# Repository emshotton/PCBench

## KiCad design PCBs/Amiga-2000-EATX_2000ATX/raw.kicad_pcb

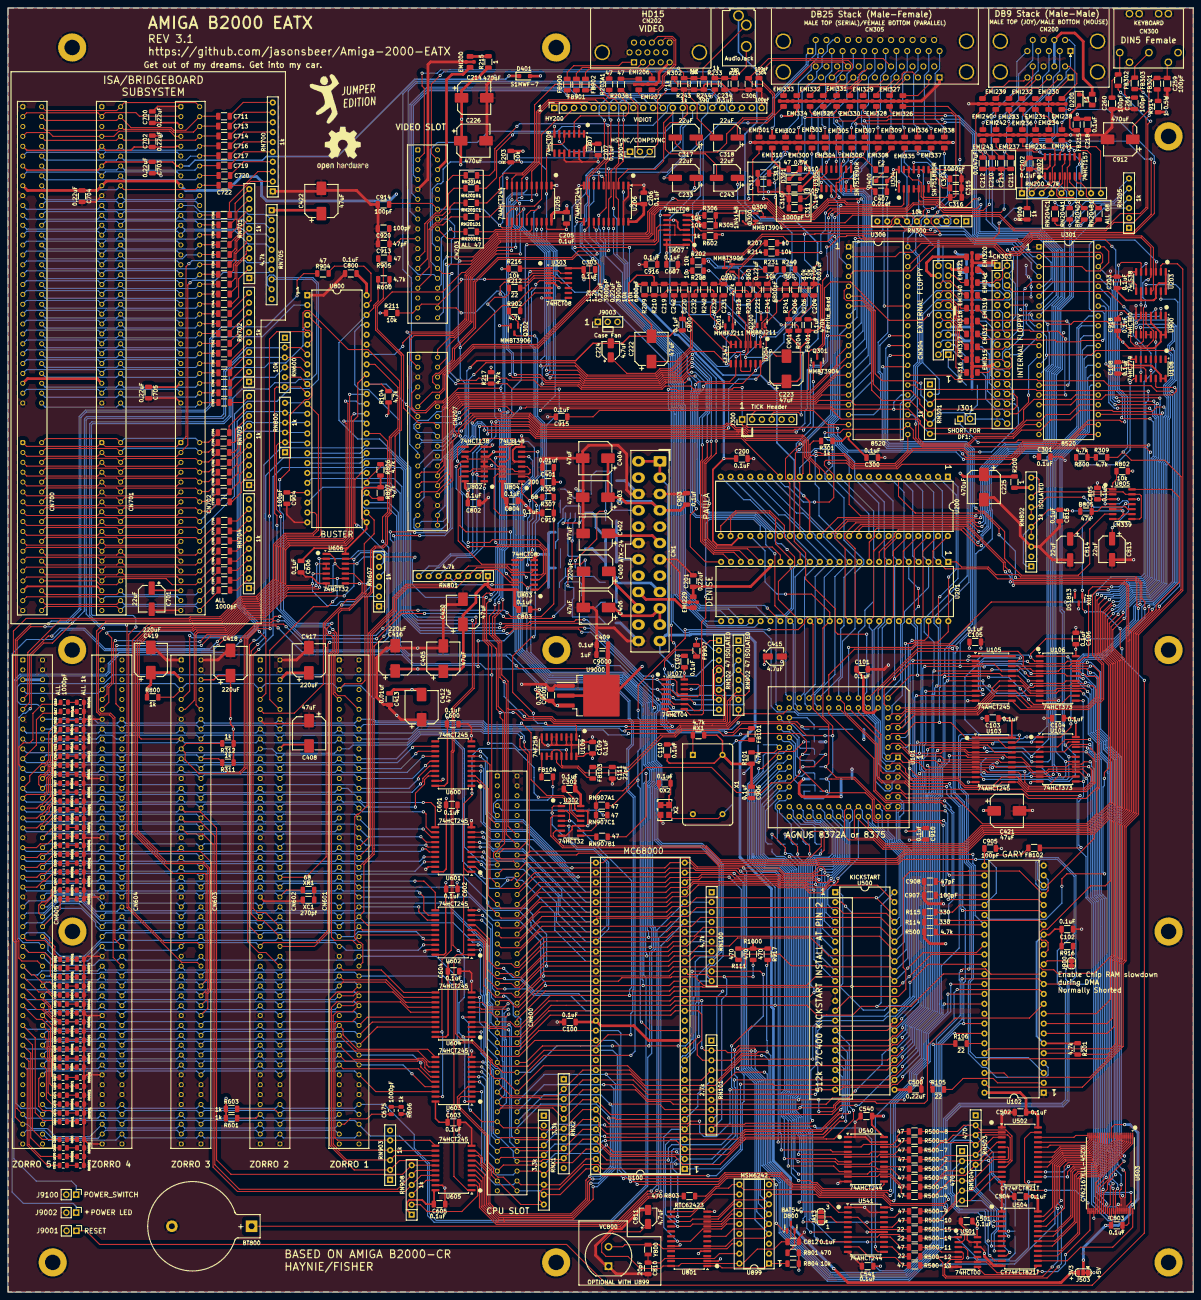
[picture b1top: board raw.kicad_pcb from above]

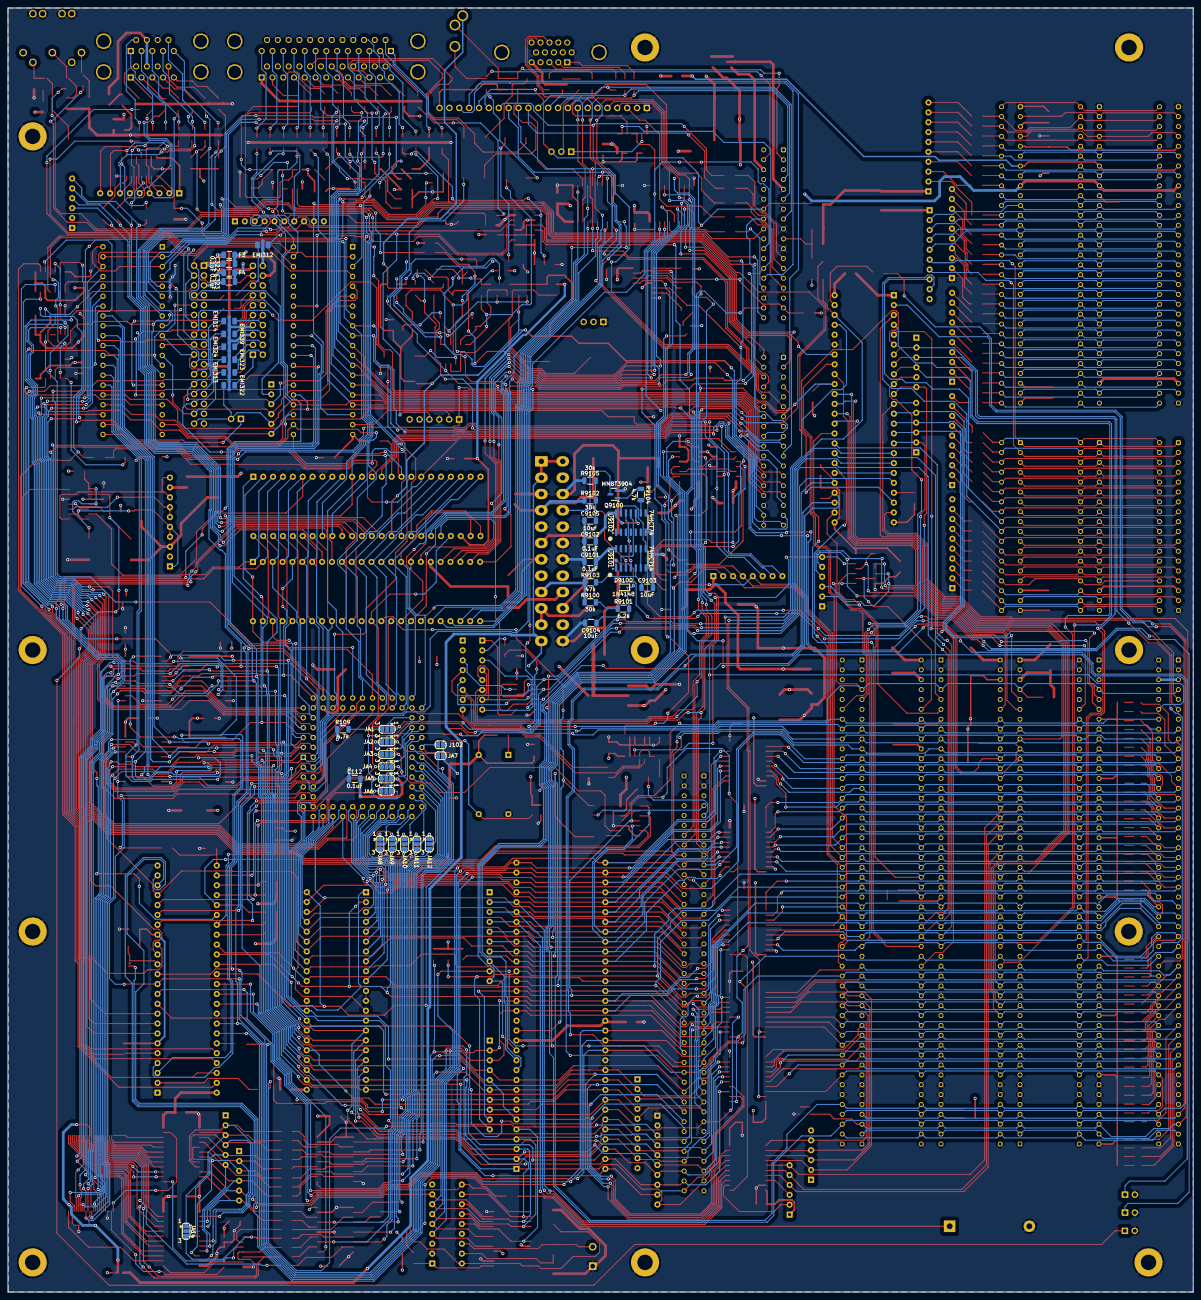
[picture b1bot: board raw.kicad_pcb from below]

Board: 4 copper layers, 304.8 x 330.2 mm, 612 parts (42 on the bottom side), 793 nets.

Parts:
BT800: Battery_Cell; BatteryHolder_Keystone_103_1x20mm
C100, C101, C102, C103, C104, C105, C106, C107, C108, C109, C110, C112, C200, C202, C203, C205, C206, C207, C218, C234, C244, C300, C301, C302, C303, C305, C322, C323, C501, C502, C503, C504, C540, C541, C600, C601, C602, C603, C604, C605, C606, C607, C800, C802, C803, C804, C805, C812, C815, C900, C901, C915, C916, C918, C919, C9101, C9102: 0.1uF; C_1206_3216Metric
C111: 22pF; C_1206_3216Metric
C201, C219, C220, C221, C500, C700, C702, C703, C704, C705: 0.22uF; C_1206_3216Metric
C204: 0.01uF; C_1206_3216Metric
C210, C211, C212, C213: 0.047uF; C_1206_3216Metric
C214, C225, C226, C912: 470uF; CP_Elec_8x10
C222, C223, C402, C403, C404, C405, C406, C408, C412, C420, C421, C422: 47uF; CP_Elec_8x10
C224, C415, C811: 4.7uF; CP_Elec_4x5.8
C231, C241: 6800pF; C_1206_3216Metric
C232, C242: 3900pF; C_1206_3216Metric
C233, C243, C317, C318, C701, C813, C814: 22uF; CP_Elec_6.3x5.8
C259, C260, C261, C304, C306, C904, C905, C907, C914, C920: 100pF; C_1206_3216Metric
C310, C311, C312, C313, C314, C315, C316, C711, C713, C714, C716, C717, C719, C720, C722, C726, C728, C730, C732, C734, C736, C738, C740, C742, C744, C746, C748, C750, C752, C754, C756, C758, C760, C762, C764, C766, C768, C770, C776, C778, C780, C782, C784, C786, C787, C789, C790, C791, C793, C794, C796: 1000pF; C_1206_3216Metric
C400, C416, C417, C418, C419: 220uF; CP_Elec_8x10
C401, C407, C413: 0.01uf; C_1206_3216Metric
C409, C903, C906, C910: 0.1uf; C_1206_3216Metric
C617, C619, C620, C621, C622, C623, C624, C625, C626, C627, C628, C629, C630, C631, C632, C633, C635, C637, C639, C641, C645, C647, C649, C650, C651, C652, C654, C655, C657, C658, C659, C660, C661, C662, C663, C664, C665, C666, C667, C668, C669, C670, C671, C672, C673, C674, C675: 1000pF; C_0805_2012Metric
C810: 20pF; C_1206_3216Metric
C908, C913: 47pF; C_1206_3216Metric
C9000: 1uF; C_1206_3216Metric
C9001: 0.33uF; C_1206_3216Metric
C9103, C9104, C9105: 10uF; C_1206_3216Metric
CN1: ATX-24; Molex_Mini-Fit_Jr_5566-24A_2x12_P4.20mm_Vertical
CN200: DB9_Male_Stack; DSUB-9_Male_Stack
CN202: DB15_Female_HighDensity; DSUB-15-HD_Female_Horizontal_P2.29x1.98mm_EdgePinOffset8.35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
CN203, CN207: Amiga-2000-Video-Slot; 2x18_P2.54mm_Horizontal
CN205: AudioJack; Jack_3.5mm_CUI_SJ1-3533NG_Horizontal_CircularHoles
CN300: KEYBOARD; DIN5
CN303: INTERNAL FLOPPY; PinHeader_2x17_P2.54mm_Vertical
CN304: EXTERNAL FLOPPY; PinHeader_2x10_P2.54mm_Vertical
CN305: DB25_Stack_FemaleAndMale; DSUB-25_Stack_Female_Bottom_Male_Top
CN600: Amiga-2000-CPU-Slot; Samtec_HLE-150-02-xx-DV-TE_2x43_P2.54mm_Horizontal
CN601, CN602, CN603, CN604, CN605: Amiga-2000-Zorro-Slot; Samtec_HLE-150-02-xx-DV-TE_2x50_P2.54mm_Horizontal
CN700, CN701, CN702: ISA-16-BIT-Slot; ISA_16-BIT_P2.54mm_Horizontal
CX2: 0.1uF; C_1206_3216Metric
D200, D301, D400, D401: S1MWF-7; D_SOD-123F
D300, D9100: 1N4148; D_SOD-323
D800: BAT54C; SOT-23
EMI200, EMI206, EMI207, EMI229, EMI230, EMI231, EMI232, EMI233, EMI234, EMI235, EMI236, EMI237, EMI238, EMI239, EMI240, EMI241, EMI242, EMI243, EMI300, EMI301, EMI302, EMI303, EMI304, EMI305, EMI306, EMI307, EMI308, EMI309, EMI310, EMI311, EMI312, EMI313, EMI314, EMI315, EMI316, EMI317, EMI318, EMI319, EMI320, EMI321, EMI322, EMI323, EMI324, EMI325, EMI326, EMI327, EMI328, EMI329, EMI330, EMI331, EMI332, EMI333, EMI334, EMI335, EMI336, EMI337, EMI338, EMI339, EMI340, EMI341: 100pF; C_1206_3216_Feedthrough
F1, F2: 4A; Fuse_1206_3216Metric
F3, F4: Fuse; Fuse_1206_3216Metric
FB101, FB102, FB103, FB104, FB215, FB301, FB302, FB303, FB401, FB900, FB901, FB902, FB907: Ferrite_Bead; C_1206_3216Metric
H1, H2, H3, H4, H5, H6, H7, H9, H10, H11, H12: MountingHole_Pad
HY200: VIDIOT; PinSocket_1x22_P2.54mm_Vertical
J102: Short for 8327A NTSC or 8375; SolderJumper-2_P1.3mm_Open_RoundedPad1.0x1.5mm
J300: TICK Header; PinHeader_1x06_P2.54mm_Vertical
J301: SHORT FOR DF1; PinHeader_1x02_P2.54mm_Vertical
J503: Mcc; SolderJumper-3_P1.3mm_Bridged12_RoundedPad1.0x1.5mm
J900: Enable Chip RAM slowdown during DMA; SolderJumper-2_P1.3mm_Bridged_RoundedPad1.0x1.5mm
J9001: RESET; PinHeader_1x02_P2.54mm_Vertical
J9002: POWER LED; PinHeader_1x02_P2.54mm_Vertical
J9003: Case Fan; FanHeader_1x03_P2.54mm_Vertical
J9004: HSYNC/COMPSYNC; PinHeader_1x03_P2.54mm_Vertical
J9100: POWER_SWITCH; PinHeader_1x02_P2.54mm_Vertical
JA1, JA2, JA3, JA4, JA5, JA6, JA8, JA9, JA10, JA11, JA12, JA13, JA14: 8375/8372A; SolderJumper-3_P1.3mm_Open_RoundedPad1.0x1.5mm
JA7: 8372A; SolderJumper-2_P1.3mm_Open_RoundedPad1.0x1.5mm
Q200, Q201: MMBFJ211; SOT-23
Q202, Q302: MMBT3906; SOT-23
Q300, Q301, Q9100: MMBT3904; SOT-23
R101, R104, R109, R201, R217, R300, R309, R500, R600, R806, R807, R902, R916, R9104: 4.7k; R_1206_3216Metric
R105, R106, R212, R500-12, R500-14, R500-15: 22; R_1206_3216Metric
R111, R801, R803, R917, R1000: 470; R_1206_3216Metric
R114, R115: 330; R_1206_3216Metric
R200, R215: 1; R_1206_3216Metric
R202, R203, R206, R211, R214, R216, R231, R232, R241, R242, R305, R306, R802, R804: 10k; R_1206_3216Metric
R203A1, R203B1, R500-1, R500-2, R500-3, R500-4, R500-5, R500-6, R500-7, R500-8, R500-9, R500-10, R500-11, R500-13, R904, R905: 47; R_1206_3216Metric
R204, R205: 470k; R_1206_3216Metric
R207, R208: 10; R_1206_3216Metric
R209, R210: 1.2k; R_1206_3216Metric
R213: 2.7k; R_1206_3216Metric
R230, R240: 360; R_1206_3216Metric
R233, R243, R301, R302, R311, R312, R601, R602, R603, R800, R900: 1k; R_1206_3216Metric
R234, R244: 390; R_1206_3216Metric
R307: 68; R_1206_3216Metric
R308: 200; R_1206_3216Metric
R310: 47 0.5W; R_1206_3216Metric
R601A1, R601B1, R601C1, R601D1, R601E1, R601F1, R601G1, R601H1, R601I1, R602A1, R602B1, R602C1, R602D1, R602E1, R602F1, R602G1, R602H1, R602I1, R603A1, R603B1, R603C1, R603D1, R603E1, R603F1, R603G1, R603H1, R603I1, R604, R604A1, R604B1, R604C1, R604D1, R604E1, R604F1, R604G1, R604H1, R604I1, R605, R605A1, R605B1, R605C1, R605D1, R605E1, R605F1, R605G1, R605H1, R606: 1k; R_0805_2012Metric
R805, R9103: 47k; R_1206_3216Metric
R914: 1 0.5W; R_1206_3216Metric
R9100, R9102, R9105: 30k; R_1206_3216Metric
R9101: 6.2k; R_1206_3216Metric
RN100, RN705: 4.7k; R_Array_SIP10
RN101: 2.7k; R_Array_SIP10
RN102, RN902: 47; R_Array_SIP8
RN200: 4.7k; R_Array_SIP9
RN201A1, RN201B1, RN201C1, RN201D1, RN203E1, RN907A1, RN907B1, RN907C1: 47; R_1206_3216Metric
RN204A1, RN204B1, RN204C1, RN204D1: 68; R_1206_3216Metric
RN205, RN301, RN607, RN800, RN903, RN908: 1k; R_Array_SIP6
RN300: 10k; R_Array_SIP10
RN503, RN504: 470; R_Array_SIP6
RN600: 10k; R_Array_SIP6
RN700, RN701, RN702, RN703, RN704, RN802: 1k; R_Array_SIP10
RN801: 4.7k; R_Array_SIP8
RNX1, RNX2: 3.3k; R_Array_SIP10
RX1: 4.7k; R_1206_3216Metric
U100: MC68000; DIP-64_W22.86mm_Socket
U101: Agnus_MULTI; PLCC-84_THT-Socket
U102: GARY; DIP-48_W15.24mm
U103, U105: 74AHCT245; SOIC-20W_7.5x12.8mm_P1.27mm
U104, U106: 74HCT373; SOIC-20W_7.5x12.8mm_P1.27mm
U107: 74HCT04; SOIC-14_3.9x8.7mm_P1.27mm
U108, U9102: 74HCT74; SOIC-14_3.9x8.7mm_P1.27mm
U109: 74F258; SOIC-16_3.9x9.9mm_P1.27mm
U200: PAULA; DIP-48_W15.24mm
U201: DENISE; DIP-48_W15.24mm
U202: 74HCT157; SOIC-16_3.9x9.9mm_P1.27mm
U203: 74LS38; SOIC-14_3.9x8.7mm_P1.27mm
U204: LF347; SOIC-14_3.9x8.7mm_P1.27mm
U205, U206, U540, U541: 74AHCT244; SOIC-20W_7.5x12.8mm_P1.27mm
U207, U303, U607, U803: 74HCT08; SOIC-14_3.9x8.7mm_P1.27mm
U300, U301: 8520; DIP-40_W15.24mm
U302, U606: 74HCT32; SOIC-14_3.9x8.7mm_P1.27mm
U304: SN75188DR; SOIC-14_3.9x8.7mm_P1.27mm
U305: SN75189DR; SOIC-14_3.9x8.7mm_P1.27mm
U500: KICKSTART; DIP-42_W15.24mm
U501, U900: 74HCT00; SOIC-14_3.9x8.7mm_P1.27mm
U502, U504: CY74FCT821T; SOIC-24W_7.5x15.4mm_P1.27mm
U503: CY62167ELL-45ZXI; TSOP-I-48_18.4x12mm_P0.5mm
U600, U601, U602, U603, U604, U605: 74HCT245; SOIC-20W_7.5x12.8mm_P1.27mm
U800: BUSTER; DIP-48_W15.24mm
U801: RTC62423; SOIC-24W_7.5x15.4mm_P1.27mm
U802: 74HCT138; SOIC-16_3.9x9.9mm_P1.27mm
U804: 74LS148; SOIC-16_3.9x9.9mm_P1.27mm
U805: LM339; SOIC-14_3.9x8.7mm_P1.27mm
U899: MSM6242; DIP-18_W7.62mm_Socket
U9000: MC7905; TO-263-3_TabPin2
U9101: 74HCT14; SOIC-14_3.9x8.7mm_P1.27mm
VC800: 22-47pF; TrimmerCap
X1: 28.63636MHz; Oscillator_DIP-14
X2: 7C-28.63636MBB-T; Oscillator_SMD_SeikoEpson_SG8002LB-4Pin_5.0x3.2mm
XC1: 270pf; C_1206_3216Metric
XR1: 68; R_1206_3216Metric
XU1: DS1813; SOT-23
Y800: 32.768KHz; Crystal_SMD_3215-2Pin_3.2x1.5mm

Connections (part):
7M: RN907A1.1, U100.15 (CLK), U201.35 (7M)
7MHz: JA3.3 (B), JA4.1 (A), RN907A1.2, RN907C1.2, U302.9
28M: CN600.9, FB104.2
+3V3: CN1.1 (+3.3V), CN1.2 (+3.3V), CN1.12 (+3.3V), CN1.13 (+3.3V), CX2.1, J503.3 (B), X2.1 (~ST), X2.4 (VCC)
+5V: C100.1, C101.1, C102.1, C103.1, C104.1, C105.1, C106.1, C107.1, C108.2, C109.2, C110.1, C202.2, C203.2, C218.1, C300.2, C301.1, C302.2, C303.1, C305.1, C323.2, C400.1, C401.1, C402.1, C403.1, C404.1, C405.1, C415.1, C416.1, C417.1, C418.1, C419.1, C420.1, C421.1, C422.1, C500.1, C501.1, C502.1, C504.1, C540.2, C541.2, C600.1, C601.1, C602.1, C603.1, C604.1, C605.2, C606.1, C607.2, C700.1, C701.1, C705.1, C800.1, C802.1, C803.1, C804.1, C805.1, C903.1, C906.1, C910.1, C918.1, CN1.4 (+5V), CN1.6 (+5V), CN1.21 (+5V), CN1.22 (+5V), CN1.23 (+5V), CN203.6, CN203.8, CN600.5, CN600.6, CN601.5, CN601.6, CN602.5, CN602.6, CN603.5, CN603.6, CN604.5, CN604.6, CN605.5, CN605.6, CN700.B3, CN700.B29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
+12V: C322.2, C406.1, C407.1, C704.1, CN1.10 (+12V), CN1.11 (+12V), CN203.10, CN600.10, CN601.10, CN602.10, CN603.10, CN604.10, CN605.10, CN700.B9, CN701.B9, CN702.B9, D400.2 (A), F3.2, J9003.2, R207.1, U304.14 (VCC)
+AUD: C200.1, C225.1, R200.2, R209.1, U200.27 (VCC)
+AV: C220.1, C222.1, C900.1, Q202.2 (E), R207.2, R213.1, U204.4 (V+)
+VID: C205.2, C206.2, C207.1, C214.1, C226.1, HY200.2, HY200.21, R215.1, U205.20 (VCC), U206.20 (VCC), U207.14 (VCC)
-5V: C412.2, C413.1, C702.1, C9001.1, CN203.31, CN600.8, CN601.8, CN602.8, CN603.8, CN604.8, CN605.8, CN700.B5, CN701.B5, CN702.B5, U9000.3 (VO)
-12V: C408.2, C409.1, C703.1, C9000.1, CN1.14 (-12V), CN601.20, CN602.20, CN603.20, CN604.20, CN605.20, CN700.B7, CN701.B7, CN702.B7, D401.1 (K), R208.2, U304.1, U9000.2 (VI)
-AV: C221.2, C223.2, C901.2, R206.2, R208.1, U204.11 (V-)
/Buster and RTC/CLKVCC: C811.1, C812.1, D800.3, U801.24 (VDD), U899.18 (VCC)
/Buster and RTC/STDP: R804.2, U801.1 (STD.P), U899.1 (STD.P)
/Floppy and Parallel/_CHNG: CN303.2, EMI341.1, RN301.2 (R1), U300.4 (PA2)
/Floppy and Parallel/_DKRST: EMI312.1, U607.6
/Floppy and Parallel/_DKWDB: CN303.22, EMI315.1, U203.8
/Floppy and Parallel/_DKWEB: CN303.24, EMI314.1, U203.11
/Floppy and Parallel/_INUSE0: CN303.6, U900.3
/Floppy and Parallel/_INUSE1: CN303.4, CN303.14, U108.9 (Q), U203.4
/Floppy and Parallel/_IORST: C916.1, EMI300.2, U607.8
/Floppy and Parallel/_KBDATA: C261.1, CN300.2, FB303.1
/Floppy and Parallel/_MTROD: CN303.16, Q301.3 (C)
/Floppy and Parallel/_MTRX: EMI311.1, U203.3
/Floppy and Parallel/_RDY: CN303.34, EMI322.1, J301.2, RN301.5 (R4), U300.7 (PA5)
/Floppy and Parallel/_TRK0: CN303.26, EMI339.1, RN301.3 (R2), U300.6 (PA4)
/Floppy and Parallel/_WPROT: CN303.28, EMI324.1, RN301.4 (R3), U300.5 (PA3)
/Memory and Kickstart/CAS: U501.6, U501.9, U501.10, U504.13 (CP)
/Memory and Kickstart/DRAB0: JA14.1 (A), R500-1.1, RN503.3 (R2), U502.2 (D0)
/Memory and Kickstart/DRAB1: R500-2.1, RN503.5 (R4), U502.3 (D1), U504.6 (D4)
/Memory and Kickstart/DRAB2: R500-3.1, RN504.2 (R1), U502.4 (D2), U504.7 (D5)
/Memory and Kickstart/DRAB3: R500-4.1, RN504.4 (R3), U502.5 (D3), U504.8 (D6)
/Memory and Kickstart/DRAB4: R500-5.1, RN503.6 (R5), U502.6 (D4), U504.9 (D7)
/Memory and Kickstart/DRAB5: R500-6.1, RN504.3 (R2), U502.7 (D5), U504.10 (D8)
/Memory and Kickstart/DRAB6: R500-7.1, RN503.4 (R3), U502.8 (D6), U504.11 (D9)
/Memory and Kickstart/DRAB7: R500-8.1, RN503.2 (R1), U502.9 (D7), U504.2 (D0)
/Memory and Kickstart/DRAB8: R500-9.1, RN504.5 (R4), U502.10 (D8), U504.3 (D1)
/Memory and Kickstart/DRAB9: R500-10.1, RN504.6 (R5), U502.11 (D9), U504.4 (D2)
/Memory and Kickstart/DRABx: JA14.2 (C), U504.5 (D3)
/Memory and Kickstart/DRAC0: U502.23 (Y0), U503.25 (A0)
/Memory and Kickstart/DRAC1: U502.22 (Y1), U503.24 (A1)
/Memory and Kickstart/DRAC2: U502.21 (Y2), U503.23 (A2)
/Memory and Kickstart/DRAC3: U502.20 (Y3), U503.22 (A3)
/Memory and Kickstart/DRAC4: U502.19 (Y4), U503.21 (A4)
/Memory and Kickstart/DRAC5: U502.18 (Y5), U503.20 (A5)
/Memory and Kickstart/DRAC6: U502.17 (Y6), U503.19 (A6)
/Memory and Kickstart/DRAC7: U502.16 (Y7), U503.18 (A7)
/Memory and Kickstart/DRAC8: U502.15 (Y8), U503.8 (A8)
/Memory and Kickstart/DRAC9: U502.14 (Y9), U503.7 (A9)
/Memory and Kickstart/DRAD1: U503.5 (A11), U504.19 (Y4)
/Memory and Kickstart/DRAD2: U503.4 (A12), U504.18 (Y5)
/Memory and Kickstart/DRAD3: U503.3 (A13), U504.17 (Y6)
/Memory and Kickstart/DRAD4: U503.2 (A14), U504.16 (Y7)
/Memory and Kickstart/DRAD5: U503.1 (A15), U504.15 (Y8)
/Memory and Kickstart/DRAD6: U503.48 (A16), U504.14 (Y9)
/Memory and Kickstart/DRAD7: U503.17 (A17), U504.23 (Y0)
/Memory and Kickstart/DRAD8: U503.16 (A18), U504.22 (Y1)
/Memory and Kickstart/DRAD9: U503.9 (A19), U504.21 (Y2)
/Memory and Kickstart/DRADx: U503.6 (A10), U504.20 (Y3)
/Memory and Kickstart/RAS: U501.3, U502.13 (CP)
/Memory and Kickstart/_MCASL: R500-11.1, U501.4, U503.15 (_BLE)
/Memory and Kickstart/_MCASU: R500-12.1, U501.5, U503.14 (_BHE)
/Memory and Kickstart/_MRAS0: R500-15.1, U501.2
/Memory and Kickstart/_MRAS1: JA14.3 (B), R500-14.1, U501.1
/Memory and Kickstart/_MWE: R500-13.1, U503.11 (_WE)
/Memory and Kickstart/_SRAMCE: U501.8, U503.26 (_CE1)
/Paula/+5VMOUSE: CN200.7, CN200.16, F1.2
/Paula/FIR0: CN200.6, EMI241.1
/Power/+5VSB: C9101.1, C9102.1, CN1.9 (+5VSB), R9100.1, R9103.1, U9101.14 (VCC), U9102.10 (~S), U9102.14 (VCC)
/Power/_PS-ON: CN1.16 (PS_ON#), Q9100.3 (C)
/Serial/CD: U301.7 (PA5), U305.11
/Serial/CTS: U301.6 (PA4), U305.6
/Serial/DSR: U301.5 (PA3), U305.8
/Serial/DTR: U301.9 (PA7), U304.12, U304.13
/Serial/RESET: C814.1, J9001.1, R805.2, U805.2, U805.10 (-), XU1.1 (/RST)
/Serial/RTS: U301.8 (PA6), U304.4, U304.5
/Video/BLUE: CN203.15, FB902.2, HY200.17
/Video/BURST: CN203.18, U205.16 (1Y1)
/Video/COMPVID: CN207.13, HY200.19
/Video/GREEN: CN203.11, FB901.2, HY200.12
/Video/PIXELSW: CN203.30, RN203E1.1
/Video/RED: CN203.7, FB900.2, HY200.7
/Video/SYNC: CN203.28, HY200.20
/Video/_COMPSYNC: C914.2, CN203.14, HY200.18, J9004.3 (B), U205.12 (1Y3)
/Zorro_Expansion/_CFGIN2: CN604.12, U606.1, U606.11
/Zorro_Expansion/_CFGIN3: CN603.12, U606.3, U606.4
/Zorro_Expansion/_CFGIN4: CN602.12, U606.6, U606.9
/Zorro_Expansion/_CFGIN5: CN601.12, U606.8
/Zorro_Expansion/_CFGOUT1: CN605.11, RN607.5 (R4), U606.13
/Zorro_Expansion/_CFGOUT2: CN604.11, RN607.4 (R3), U606.2
/Zorro_Expansion/_CFGOUT3: CN603.11, RN607.3 (R2), U606.5
/Zorro_Expansion/_CFGOUT4: CN602.11, RN607.2 (R1), U606.10
A1: CN600.29, U100.29 (A1), U101.60 (A1), U500.10 (A0), U600.2 (A0)
A2: CN600.27, U100.30 (A2), U101.61 (A2), U500.9 (A1), U600.3 (A1), U801.5 (A0), U899.4 (A0)
A3: CN600.26, U100.31 (A3), U101.62 (A3), U500.8 (A2), U600.5 (A3), U801.7 (A1), U899.5 (A1)
A4: CN600.24, U100.32 (A4), U101.63 (A4), U500.7 (A3), U600.7 (A5), U801.9 (A2), U899.6 (A2)
A5: CN600.21, U100.33 (A5), U101.64 (A5), U500.6 (A4), U600.8 (A6), U801.10 (A3), U899.7 (A3)
A6: CN600.23, U100.34 (A6), U101.65 (A6), U500.5 (A5), U600.6 (A4)
A7: CN600.28, U100.35 (A7), U101.66 (A7), U500.4 (A6), U600.4 (A2)
A8: CN600.30, U100.36 (A8), U101.67 (A8), U300.38 (RS0), U301.38 (RS0), U500.3 (A7), U601.9 (A7)
A9: CN600.32, U100.37 (A9), U101.68 (A9), U300.37 (RS1), U301.37 (RS1), U500.41 (A8), U601.8 (A6)
A10: CN600.34, U100.38 (A10), U101.69 (A10), U300.36 (RS2), U301.36 (RS2), U500.40 (A9), U601.7 (A5)
A11: CN600.36, U100.39 (A11), U101.70 (A11), U300.35 (RS3), U301.35 (RS3), U500.39 (A10), U601.6 (A4)
A12: CN600.38, U100.40 (A12), U101.71 (A12), U302.1, U500.38 (A11), U601.5 (A3)
A13: CN600.39, U100.41 (A13), U101.72 (A13), U302.5, U500.37 (A12), U601.4 (A2)
A14: CN600.41, U100.42 (A14), U101.73 (A14), U500.36 (A13), U601.3 (A1)
A15: CN600.43, U100.43 (A15), U101.74 (A15), U500.35 (A14), U601.2 (A0)
A16: CN600.45, U100.44 (A16), U101.75 (A16), U500.34 (A15), U602.9 (A7)
A17: CN600.47, U100.45 (A17), U101.76 (A17), U102.33 (A17), U500.33 (A16), U602.8 (A6)
A18: CN600.52, U100.46 (A18), U101.77 (A18), U102.34 (A18), U500.2 (A17), U602.7 (A5)
A19: CN600.54, U100.47 (A19), U101.59 (A19), U102.35 (A19), U500.1 (A18), U602.6 (A4)
A20: CN600.56, JA2.1 (A), U100.48 (A20), U102.36 (A20), U500.42 (A19), U602.5 (A3)
A21: CN600.58, U100.50 (A21), U102.37 (A21), U602.4 (A2)
A22: CN600.57, U100.51 (A22), U102.38 (A22), U602.3 (A1)
A23: CN600.59, U100.52 (A23), U102.39 (A23), U602.2 (A0)
AUDIN: C317.1, R202.1
AUDIO: C204.2, C210.2, C211.2, C212.2, C213.2, C219.2, C220.2, C221.1, C222.2, C223.1, C224.2, C232.2, C242.2, C900.2, C901.1, CN205.S, CN207.34, CN207.36, FB401.2, R210.2, U200.34 (A_GND)
AUDOUT: C243.2, R243.2, R302.1
AgnusCLK: C111.1, FB103.1, U101.34 (28MHz)
B0: HY200.16, RN201A1.1, U206.9 (2Y3)
B1: CN207.10, HY200.15, U206.7 (2Y2)
B2: CN207.11, HY200.14, U206.5 (2Y1)
B3: HY200.13, RN201B1.1, U206.3 (2Y0)
BA1: C624.2, CN601.29, CN602.29, CN603.29, CN604.29, CN605.29, U600.18 (B0)
BA2: C622.2, CN601.27, CN602.27, CN603.27, CN604.27, CN605.27, U600.17 (B1)
BA3: C621.2, CN601.26, CN602.26, CN603.26, CN604.26, CN605.26, U600.15 (B3)
BA4: C620.2, CN601.24, CN602.24, CN603.24, CN604.24, CN605.24, U600.13 (B5)
BA5: C617.2, CN601.21, CN602.21, CN603.21, CN604.21, CN605.21, U600.12 (B6)
BA6: C619.2, CN601.23, CN602.23, CN603.23, CN604.23, CN605.23, U600.14 (B4)
BA7: C623.2, CN601.28, CN602.28, CN603.28, CN604.28, CN605.28, U600.16 (B2)
BA8: C625.2, CN601.30, CN602.30, CN603.30, CN604.30, CN605.30, U601.11 (B7)
BA9: C627.2, CN601.32, CN602.32, CN603.32, CN604.32, CN605.32, U601.12 (B6)
BA10: C629.2, CN601.34, CN602.34, CN603.34, CN604.34, CN605.34, U601.13 (B5)
BA11: C631.2, CN601.36, CN602.36, CN603.36, CN604.36, CN605.36, U601.14 (B4)
BA12: C632.2, CN601.38, CN602.38, CN603.38, CN604.38, CN605.38, U601.15 (B3)
BA13: C633.2, CN601.39, CN602.39, CN603.39, CN604.39, CN605.39, U601.16 (B2)
BA14: C635.2, CN601.41, CN602.41, CN603.41, CN604.41, CN605.41, U601.17 (B1)
BA15: C637.2, CN601.43, CN602.43, CN603.43, CN604.43, CN605.43, U601.18 (B0)
BA16: C639.2, CN601.45, CN602.45, CN603.45, CN604.45, CN605.45, U602.11 (B7)
BA17: C641.2, CN601.47, CN602.47, CN603.47, CN604.47, CN605.47, U602.12 (B6)
BA18: C645.2, CN601.52, CN602.52, CN603.52, CN604.52, CN605.52, U602.13 (B5)
BA19: C647.2, CN601.54, CN602.54, CN603.54, CN604.54, CN605.54, U602.14 (B4), U800.30 (A19)
BA20: C649.2, CN601.56, CN602.56, CN603.56, CN604.56, CN605.56, U602.15 (B3), U800.31 (A20)
BA21: C651.2, CN601.58, CN602.58, CN603.58, CN604.58, CN605.58, U602.16 (B2), U800.32 (A21)
BA22: C650.2, CN601.57, CN602.57, CN603.57, CN604.57, CN605.57, U602.17 (B1), U800.33 (A22)
BA23: C652.2, CN601.59, CN602.59, CN603.59, CN604.59, CN605.59, U602.18 (B0), U800.34 (A23)
BD0: C664.2, CN601.75, CN602.75, CN603.75, CN604.75, CN605.75, U603.11 (B7)
BD1: C666.2, CN601.77, CN602.77, CN603.77, CN604.77, CN605.77, U603.12 (B6)
BD2: C668.2, CN601.79, CN602.79, CN603.79, CN604.79, CN605.79, U603.13 (B5)
BD3: C670.2, CN601.81, CN602.81, CN603.81, CN604.81, CN605.81, U603.14 (B4)
BD4: C672.2, CN601.83, CN602.83, CN603.83, CN604.83, CN605.83, U603.16 (B2)
BD5: C674.2, CN601.86, CN602.86, CN603.86, CN604.86, CN605.86, U603.18 (B0)
BD6: C673.2, CN601.84, CN602.84, CN603.84, CN604.84, CN605.84, U603.17 (B1)
BD7: C671.2, CN601.82, CN602.82, CN603.82, CN604.82, CN605.82, U603.15 (B3)
BD8: C669.2, CN601.80, CN602.80, CN603.80, CN604.80, CN605.80, U604.18 (B0)
BD9: C667.2, CN601.78, CN602.78, CN603.78, CN604.78, CN605.78, U604.17 (B1)
BD10: C665.2, CN601.76, CN602.76, CN603.76, CN604.76, CN605.76, U604.16 (B2)
BD11: C661.2, CN601.71, CN602.71, CN603.71, CN604.71, CN605.71, U604.15 (B3)
BD12: C659.2, CN601.69, CN602.69, CN603.69, CN604.69, CN605.69, U604.14 (B4)
BD13: C657.2, CN601.67, CN602.67, CN603.67, CN604.67, CN605.67, U604.13 (B5)
BD14: C655.2, CN601.65, CN602.65, CN603.65, CN604.65, CN605.65, U604.12 (B6)
BD15: C654.2, CN601.63, CN602.63, CN603.63, CN604.63, CN605.63, U604.11 (B7)
BFC0: C626.2, CN601.31, CN602.31, CN603.31, CN604.31, CN605.31, RN908.6 (R5), U605.15 (B3)
BFC1: C628.2, CN601.33, CN602.33, CN603.33, CN604.33, CN605.33, RN908.5 (R4), U605.16 (B2)
BFC2: C630.2, CN601.35, CN602.35, CN603.35, CN604.35, CN605.35, RN908.4 (R3), U605.17 (B1)
C1: C907.1, JA5.3 (B), JA6.1 (A), U102.28 (CCK), U107.3, U107.13, U200.28 (CCK), U201.36 (CCK), U800.19 (C1)
C3: C908.1, JA3.1 (A), JA6.3 (B), U102.27 (CCKQ), U107.5, U107.9, U200.29 (CCKQ), U800.20 (C3)
D0: CN600.75, RNX1.3 (R2), U100.5 (D0), U105.2 (A0), U106.2 (O0), U300.33 (D0), U500.14 (D0), U603.9 (A7), U801.19 (D0), U899.14 (D0)
D1: CN600.77, RNX1.4 (R3), U100.4 (D1), U105.3 (A1), U106.5 (O1), U300.32 (D1), U500.16 (D1), U603.8 (A6), U801.16 (D1), U899.13 (D1)
D2: CN600.79, RNX1.5 (R4), U100.3 (D2), U105.4 (A2), U106.6 (O2), U300.31 (D2), U500.18 (D2), U603.7 (A5), U801.15 (D2), U899.12 (D2)
D3: CN600.81, RNX1.6 (R5), U100.2 (D3), U105.5 (A3), U106.9 (O3), U300.30 (D3), U500.20 (D3), U603.6 (A4), U801.14 (D3), U899.11 (D3)
D4: CN600.83, RNX1.10 (R9), U100.1 (D4), U105.6 (A4), U106.12 (O4), U300.29 (D4), U500.23 (D4), U603.4 (A2)
D5: CN600.86, RNX1.9 (R8), U100.64 (D5), U105.7 (A5), U106.15 (O5), U300.28 (D5), U500.25 (D5), U603.2 (A0)
D6: CN600.84, RNX1.8 (R7), U100.63 (D6), U105.8 (A6), U106.16 (O6), U300.27 (D6), U500.27 (D6), U603.3 (A1)
D7: CN600.82, RNX1.7 (R6), U100.62 (D7), U105.9 (A7), U106.19 (O7), U300.26 (D7), U500.29 (D7), U603.5 (A3)
D8: CN600.80, RNX2.9 (R8), U100.61 (D8), U103.2 (A0), U104.2 (O0), U301.33 (D0), U500.15 (D8), U604.2 (A0)
D9: CN600.78, RNX2.8 (R7), U100.60 (D9), U103.3 (A1), U104.5 (O1), U301.32 (D1), U500.17 (D9), U604.3 (A1)
D10: CN600.76, RNX2.7 (R6), U100.59 (D10), U103.4 (A2), U104.6 (O2), U301.31 (D2), U500.19 (D10), U604.4 (A2)
D11: CN600.71, RNX2.6 (R5), U100.58 (D11), U103.5 (A3), U104.9 (O3), U301.30 (D3), U500.21 (D11), U604.5 (A3)
D12: CN600.69, RNX2.5 (R4), U100.57 (D12), U103.6 (A4), U104.12 (O4), U301.29 (D4), U500.24 (D12), U604.6 (A4)
D13: CN600.67, RNX2.4 (R3), U100.56 (D13), U103.7 (A5), U104.15 (O5), U301.28 (D5), U500.26 (D13), U604.7 (A5)
D14: CN600.65, RNX2.3 (R2), U100.55 (D14), U103.8 (A6), U104.16 (O6), U301.27 (D6), U500.28 (D14), U604.8 (A6)
D15: CN600.63, RNX2.2 (R1), U100.54 (D15), U103.9 (A7), U104.19 (O7), U301.26 (D7), U500.30 (D15), U604.9 (A7)
DIR: CN303.18, EMI317.1, U301.11 (PB1)
DKWE: U102.8 (DKWE), U200.39 (DKWE)
DMAL: U101.18 (DMAL), U200.12 (DMAL)
DMAOUT: U302.11, U600.1 (A->B), U601.1 (A->B), U602.1 (A->B), U605.1 (A->B)
DOE: CN601.93, CN602.93, CN603.93, CN604.93, CN605.93, R601.2, R904.1
DRA0-G: JA7.1 (A), U101.42 (DRA0/GND), U540.2 (I0a)
DRA1-0: U101.43 (DRA1/DRA0), U540.4 (I1a)
DRA2-1: U101.44 (DRA2/DRA1), U540.6 (I2a)
DRA3-2: U101.45 (DRA3/DRA2), U540.8 (I3a)
DRA4-3: U101.46 (DRA4/DRA3), U540.11 (I0b)
DRA5-4: U101.47 (DRA5/DRA4), U540.13 (I1b)
DRA6-5: U101.48 (DRA6/DRA5), U540.15 (I2b)
DRA7-6: U101.49 (DRA7/DRA6), U540.17 (I3b)
DRA8: JA12.3 (B), JA13.3 (B)
DRA8-7: U101.50 (DRA8/DRA7), U541.2 (I0a)
DRA9: JA8.1 (A), JA13.1 (A)
DRD0: U101.14 (DRD0), U105.18 (B0), U106.3 (D0), U200.10 (DRD0), U201.7 (DRD0), U503.29 (O0)
DRD1: U101.13 (DRD1), U105.17 (B1), U106.4 (D1), U200.9 (DRD1), U201.6 (DRD1), U503.31 (O1)
DRD2: U101.12 (DRD2), U105.16 (B2), U106.7 (D2), U200.7 (DRD2), U201.5 (DRD2), U503.33 (O2)
DRD3: U101.11 (DRD3), U105.15 (B3), U106.8 (D3), U200.6 (DRD3), U201.4 (DRD3), U503.35 (O3)
DRD4: U101.10 (DRD4), U105.14 (B4), U106.13 (D4), U200.5 (DRD4), U201.3 (DRD4), U503.38 (O4)
DRD5: U101.9 (DRD5), U105.13 (B5), U106.14 (D5), U200.4 (DRD5), U201.2 (DRD5), U503.40 (O5)
DRD6: U101.8 (DRD6), U105.12 (B6), U106.17 (D6), U200.3 (DRD6), U201.1 (DRD6), U503.42 (O6)
DRD7: U101.7 (DRD7), U105.11 (B7), U106.18 (D7), U200.2 (DRD7), U201.48 (DRD7), U503.44 (O7)
DRD8: U101.6 (DRD8), U103.18 (B0), U104.3 (D0), U200.1 (DRD8), U201.47 (DRD8), U503.30 (O8)
DRD9: U101.5 (DRD9), U103.17 (B1), U104.4 (D1), U200.48 (DRD9), U201.46 (DRD9), U503.32 (O9)
DRD10: U101.4 (DRD10), U103.16 (B2), U104.7 (D2), U200.47 (DRD10), U201.45 (DRD10), U503.34 (O10)
DRD11: U101.3 (DRD11), U103.15 (B3), U104.8 (D3), U200.46 (DRD11), U201.44 (DRD11), U503.36 (O11)
DRD12: U101.2 (DRD12), U103.14 (B4), U104.13 (D4), U200.45 (DRD12), U201.43 (DRD12), U503.39 (O12)
DRD13: U101.1 (DRD13), U103.13 (B5), U104.14 (D5), U200.44 (DRD13), U201.42 (DRD13), U503.41 (O13)
DRD14: U101.84 (DRD14), U103.12 (B6), U104.17 (D6), U200.43 (DRD14), U201.41 (DRD14), U503.43 (014)
DRD15: U101.83 (DRD15), U103.11 (B7), U104.18 (D7), U200.42 (DRD15), U201.40 (DRD15), U503.45 (O15)
E: CN600.50, CN601.50, CN602.50, CN603.50, CN604.50, CN605.50, U100.20 (E), U300.25 (E), U301.25 (E), XR1.1
E7M: CN601.92, CN602.92, CN603.92, CN604.92, CN605.92, RN907B1.1
ECDAC: CN601.15, CN602.15, CN603.15, CN604.15, CN605.15, RN902.8 (R4.2)
FC0: CN600.31, RN100.2 (R1), U100.28 (FC0), U605.5 (A3)
FC1: CN600.33, RN100.3 (R2), U100.27 (FC1), U605.4 (A2)
FC2: CN600.35, RN100.4 (R3), U100.26 (FC2), U605.3 (A1)
FLTLEFT: C244.1, CN203.3, CN205.T, R243.1, R244.2
FLTRIGHT: C234.1, CN203.4, CN205.R, R233.1, R234.2
G0: CN207.6, HY200.11, U206.12 (1Y3)
G1: CN207.7, HY200.10, U206.14 (1Y2)
G2: CN207.8, HY200.9, U206.16 (1Y1)
G3: HY200.8, RN201C1.1, U206.18 (1Y0)
GND: BT800.2 (-), C100.2, C101.2, C102.2, C103.2, C104.2, C105.2, C106.2, C107.2, C108.1, C109.1, C110.2, C111.2, C112.1, C200.2, C201.2, C202.1, C203.1, C205.1, C206.1, C207.2, C214.2, C218.2, C225.2, C226.2, C234.2, C244.2, C259.2, C260.2, C261.2, C300.1, C301.2, C302.1, C303.2, C304.2, C305.2, C306.2, C310.2, C311.2, C312.2, C313.2, C314.1, C315.1, C316.1, C322.1, C323.1, C400.2, C401.2, C402.2, C403.2, C404.2, C405.2, C406.2, C407.2, C408.1, C409.2, C412.1, C413.2, C415.2, C416.2, C417.2, C418.2, C419.2, C420.2, C421.2, C422.2, C500.2, C501.2, C502.2, C503.2, C504.2, C540.1, C541.1, C600.2, C601.2, C602.2, C603.2, C604.2, C605.1, C606.2, C607.1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
M0H: RN204D1.2, RN205.4 (R3), U201.9 (M0H)
M0V: RN204C1.2, RN205.6 (R5), U201.38 (M0V)
M1H: RN204B1.2, RN205.3 (R2), U201.8 (M1H)
M1V: RN204A1.2, RN205.5 (R4), U201.39 (M1V)
Mcc: C503.1, J503.2 (C), U503.12 (CE2), U503.37 (Vcc), U503.47 (_BYTE)
unnamed: BT800.1 (+), R803.1
unnamed: C231.2, R231.1, R232.2
unnamed: C233.2, R233.2
unnamed: C241.2, R241.1, R242.2
unnamed: C259.1, C912.1, CN300.5, FB301.1
unnamed: C260.1, CN300.1, FB302.1
unnamed: C304.1, C318.1, CN305.36
unnamed: C306.1, C317.2, CN305.43
unnamed: C310.1, EMI331.1, U305.13
unnamed: C311.1, EMI330.1, U305.10
unnamed: C312.1, EMI329.1, U305.4
unnamed: C313.1, EMI328.1, U305.1
unnamed: C314.2, EMI325.1, U304.11
unnamed: C315.2, EMI326.1, U304.8
unnamed: C316.2, EMI327.1, U304.6
unnamed: C318.2, R302.2
unnamed: C617.1, R601A1.2
unnamed: C619.1, R601B1.2
unnamed: C620.1, R601C1.2
unnamed: C621.1, R601D1.2
unnamed: C622.1, R601E1.2
unnamed: C623.1, R601F1.2
unnamed: C624.1, R601G1.2
unnamed: C625.1, R601H1.2
unnamed: C626.1, R601I1.2
unnamed: C627.1, R602A1.2
unnamed: C628.1, R602B1.2
unnamed: C629.1, R602C1.2
unnamed: C630.1, R602D1.2
unnamed: C631.1, R602E1.2
unnamed: C632.1, R602F1.2
unnamed: C633.1, R602G1.2
unnamed: C635.1, R602H1.2
unnamed: C637.1, R602I1.2
unnamed: C639.1, R603A1.2
unnamed: C641.1, R603B1.2
unnamed: C645.1, R603C1.2
unnamed: C647.1, R603D1.2
unnamed: C649.1, R603E1.2
unnamed: C650.1, R603F1.2
unnamed: C651.1, R603G1.2
unnamed: C652.1, R603H1.2
unnamed: C654.1, R603I1.2
unnamed: C655.1, R604A1.2
unnamed: C657.1, R604B1.2
unnamed: C658.1, R604C1.2
unnamed: C659.1, R604D1.2
unnamed: C660.1, R604E1.2
unnamed: C661.1, R604F1.2
unnamed: C662.1, R604G1.2
unnamed: C663.1, R604H1.2
unnamed: C664.1, R604I1.2
unnamed: C665.1, R604.2
unnamed: C666.1, R605.2
unnamed: C667.1, R605A1.2
unnamed: C668.1, R605B1.2
unnamed: C669.1, R605C1.2
unnamed: C670.1, R605D1.2
unnamed: C671.1, R605E1.2
unnamed: C672.1, R605F1.2
unnamed: C673.1, R605G1.2
unnamed: C674.1, R605H1.2
unnamed: C675.1, R606.2
unnamed: C711.2, CN700.A2, CN701.A2, CN702.A2
unnamed: C713.2, CN700.A3, CN701.A3, CN702.A3
unnamed: C714.2, CN700.A4, CN701.A4, CN702.A4
unnamed: C716.2, CN700.A5, CN701.A5, CN702.A5
unnamed: C717.2, CN700.A6, CN701.A6, CN702.A6
unnamed: C719.2, CN700.A7, CN701.A7, CN702.A7
unnamed: C720.2, CN700.A8, CN701.A8, CN702.A8
unnamed: C722.2, CN700.A9, CN701.A9, CN702.A9
unnamed: C726.2, CN700.A12, CN701.A12, CN702.A12
unnamed: C728.2, CN700.A13, CN701.A13, CN702.A13
unnamed: C730.2, CN700.A14, CN701.A14, CN702.A14
unnamed: C732.2, CN700.A15, CN701.A15, CN702.A15
unnamed: C734.2, CN700.A16, CN701.A16, CN702.A16
unnamed: C736.2, CN700.A17, CN701.A17, CN702.A17
unnamed: C738.2, CN700.A18, CN701.A18, CN702.A18
unnamed: C740.2, CN700.A19, CN701.A19, CN702.A19
unnamed: C742.2, CN700.A20, CN701.A20, CN702.A20
unnamed: C744.2, CN700.A21, CN701.A21, CN702.A21
unnamed: C746.2, CN700.A22, CN701.A22, CN702.A22
unnamed: C748.2, CN700.A23, CN701.A23, CN702.A23
unnamed: C750.2, CN700.A24, CN701.A24, CN702.A24
unnamed: C752.2, CN700.A25, CN701.A25, CN702.A25
unnamed: C754.2, CN700.A26, CN701.A26, CN702.A26
unnamed: C756.2, CN700.A27, CN701.A27, CN702.A27
unnamed: C758.2, CN700.A28, CN701.A28, CN702.A28
unnamed: C760.2, CN700.C3, CN701.C3, CN702.C3
unnamed: C762.2, CN700.C4, CN701.C4, CN702.C4
unnamed: C764.2, CN700.C5, CN701.C5, CN702.C5
unnamed: C766.2, CN700.C6, CN701.C6, CN702.C6
unnamed: C768.2, CN700.C7, CN701.C7, CN702.C7
unnamed: C770.2, CN700.C8, CN701.C8, CN702.C8
unnamed: C776.2, CN700.C11, CN701.C11, CN702.C11
unnamed: C778.2, CN700.C12, CN701.C12, CN702.C12
unnamed: C780.2, CN700.C13, CN701.C13, CN702.C13
unnamed: C782.2, CN700.C14, CN701.C14, CN702.C14
unnamed: C784.2, CN700.C15, CN701.C15, CN702.C15
unnamed: C786.2, CN700.C16, CN701.C16, CN702.C16
unnamed: C787.2, CN700.C17, CN701.C17, CN702.C17
unnamed: C789.2, CN700.C18, CN701.C18, CN702.C18
unnamed: C790.2, CN700.A29, CN701.A29, CN702.A29
unnamed: C791.2, CN700.A30, CN701.A30, CN702.A30
unnamed: C793.2, CN700.A31, CN701.A31, CN702.A31
unnamed: C794.2, CN700.C1, CN701.C1, CN702.C1
unnamed: C796.2, CN700.C2, CN701.C2, CN702.C2
unnamed: C9103.1, R9103.2, U9101.5
unnamed: C9105.1, R9102.2, R9105.1, U9101.3
unnamed: CN200.1, EMI234.2
unnamed: CN200.2, EMI235.2
unnamed: CN200.3, EMI236.2
unnamed: CN200.4, EMI237.2
unnamed: CN200.5, EMI243.2
unnamed: CN200.9, EMI242.2
unnamed: CN200.10, EMI230.2
unnamed: CN200.11, EMI231.2
unnamed: CN200.12, EMI232.2
unnamed: CN200.13, EMI233.2
unnamed: CN200.14, EMI240.1
unnamed: CN200.15, EMI238.1
unnamed: CN200.18, EMI239.1
unnamed: CN202.1, FB900.1
unnamed: CN202.2, FB901.1
unnamed: CN202.3, FB902.1
unnamed: CN202.13, EMI206.2
unnamed: CN202.14, EMI207.2
unnamed: CN203.23, RN201A1.2
unnamed: CN203.25, RN201B1.2
unnamed: CN203.27, RN201C1.2
unnamed: CN203.29, RN201D1.2
unnamed: CN203.33, R211.2, U303.2
unnamed: CN304.1, EMI322.2
unnamed: CN304.2, EMI313.2
unnamed: CN304.3, EMI323.2
unnamed: CN304.4, EMI324.2
unnamed: CN304.6, EMI339.2
unnamed: CN304.8, EMI314.2
unnamed: CN304.9, EMI315.2
unnamed: CN304.10, EMI316.2
unnamed: CN304.11, EMI317.2
unnamed: CN304.12, EMI311.2
unnamed: CN304.13, EMI318.2
unnamed: CN304.14, EMI319.2
unnamed: CN304.15, EMI312.2
unnamed: CN304.16, EMI340.2
unnamed: CN304.17, EMI341.2
unnamed: CN304.18, EMI320.2
unnamed: CN304.19, EMI321.2
unnamed: CN305.1, EMI301.2
unnamed: CN305.2, EMI302.2
unnamed: CN305.3, EMI303.2
unnamed: CN305.4, EMI304.2
unnamed: CN305.5, EMI305.2
unnamed: CN305.6, EMI306.2
unnamed: CN305.7, EMI307.2
unnamed: CN305.8, EMI308.2
unnamed: CN305.9, EMI309.2
unnamed: CN305.10, EMI335.2
unnamed: CN305.11, EMI336.2
unnamed: CN305.12, EMI337.2
unnamed: CN305.13, EMI338.2
unnamed: CN305.27, EMI326.2
unnamed: CN305.28, EMI328.2
unnamed: CN305.29, EMI327.2
unnamed: CN305.30, EMI329.2
unnamed: CN305.31, EMI330.2
unnamed: CN305.33, EMI331.2
unnamed: CN305.34, EMI332.1
unnamed: CN305.35, EMI334.1
unnamed: CN305.45, EMI325.2
unnamed: CN305.47, EMI333.1
unnamed: CN305.14, EMI310.1
unnamed: CN305.16, EMI300.1
unnamed: CN601.97, CN602.97, CN603.97, CN604.97, CN605.97
unnamed: CN601.98, CN602.98, CN603.98, CN604.98, CN605.98
unnamed: CN700.A1, CN701.A1, CN702.A1
unnamed: CN700.A10, CN701.A10, CN702.A10
unnamed: CN700.A11, CN701.A11, CN702.A11
unnamed: CN700.B2, CN701.B2, CN702.B2
unnamed: CN700.B4, CN701.B4, CN702.B4
unnamed: CN700.B6, CN701.B6, CN702.B6
unnamed: CN700.B8, CN701.B8, CN702.B8
unnamed: CN700.B15, CN701.B15, CN702.B15
unnamed: CN700.B16, CN701.B16, CN702.B16
unnamed: CN700.B17, CN701.B17, CN702.B17
unnamed: CN700.B18, CN701.B18, CN702.B18
unnamed: CN700.B19, CN701.B19, CN702.B19
unnamed: CN700.B20, CN701.B20, CN702.B20
unnamed: CN700.B21, CN701.B21, CN702.B21
unnamed: CN700.B22, CN701.B22, CN702.B22
unnamed: CN700.B23, CN701.B23, CN702.B23
unnamed: CN700.B24, CN701.B24, CN702.B24
unnamed: CN700.B25, CN701.B25, CN702.B25
unnamed: CN700.B26, CN701.B26, CN702.B26
unnamed: CN700.B27, CN701.B27, CN702.B27
unnamed: CN700.B28, CN701.B28, CN702.B28
unnamed: CN700.B30, CN701.B30, CN702.B30
unnamed: CN700.D3, CN701.D3, CN702.D3
unnamed: CN700.D4, CN701.D4, CN702.D4
unnamed: CN700.D5, CN701.D5, CN702.D5
unnamed: CN700.D6, CN701.D6, CN702.D6
unnamed: CN700.D7, CN701.D7, CN702.D7
unnamed: CN700.D8, CN701.D8, CN702.D8
unnamed: CN700.D9, CN701.D9, CN702.D9
unnamed: CN700.D10, CN701.D10, CN702.D10
unnamed: CN700.D11, CN701.D11, CN702.D11
unnamed: CN700.D12, CN701.D12, CN702.D12
unnamed: CN700.D13, CN701.D13, CN702.D13
unnamed: CN700.D14, CN701.D14, CN702.D14
unnamed: CN700.D15, CN701.D15, CN702.D15
unnamed: CN700.D17, CN701.D17, CN702.D17
unnamed: D200.2 (A), FB215.2
unnamed: D200.1 (K), F1.1
unnamed: D300.1 (K), Q300.1 (B), R305.1, R306.2
unnamed: D301.1 (K), R310.2
unnamed: D400.1 (K), F2.1
unnamed: D401.2 (A), EMI334.2
unnamed: D800.1, R803.2
unnamed: D800.2, R801.2
unnamed: D9100.2 (A), J9100.1, R9100.2, R9101.2
unnamed: C9104.1, D9100.1 (K), R9101.1, U9101.1
unnamed: EMI200.2, R215.2
unnamed: EMI206.1, R203B1.1
unnamed: EMI207.1, R203A1.1
unnamed: EMI310.2, R310.1
unnamed: EMI320.1, F3.1
unnamed: EMI321.1, F4.1
unnamed: EMI332.2, F2.2
unnamed: EMI333.2, R306.1
unnamed: FB301.2, R914.2
unnamed: J102.2 (B), R101.2, U101.41 (GND/PAL-NTSC)
unnamed: J301.1, U203.6
unnamed: J900.2 (B), R916.1, U102.14 (_BGACK)
unnamed: C919.1, J9002.1, R307.1, R308.2
unnamed: J9004.1 (A), U207.6
unnamed: J9004.2 (C), R203B1.2
unnamed: JA1.3 (B), R109.2
unnamed: JA1.2 (C), U101.36 (_CDAC/_XCLKEN)
unnamed: JA2.2 (C), U101.35 (A20/XCLK)
unnamed: JA3.2 (C), U101.38 (CCKQ/7MHz)
unnamed: JA4.2 (C), U101.37 (7MHz/_CDAC)
unnamed: C112.2, JA5.1 (A)
unnamed: JA5.2 (C), U101.40 (14M_or_Vbb/CCK)
unnamed: JA6.2 (C), U101.39 (CCK/CCKQ)
unnamed: JA8.2 (C), U101.55 (DRA9/_CASU)
unnamed: JA9.2 (C), U101.54 (_CASU/_CASL)
unnamed: JA10.2 (C), U101.53 (_CASL/_UDS)
unnamed: JA11.2 (C), U101.52 (_UDS/_LDS)
unnamed: JA12.2 (C), U101.51 (_LDS/DRA8)
unnamed: JA13.2 (C), U541.4 (I1a)
unnamed: Q200.3 (G), R204.2
unnamed: C242.1, Q200.1 (S), R242.1, U204.3 (+)
unnamed: Q201.3 (G), R205.2
unnamed: C232.1, Q201.1 (S), R232.1, U204.5 (-)
unnamed: Q202.1 (B), R213.2, R214.2
unnamed: C204.1, Q202.3 (C), R204.1, R205.1, R206.1
unnamed: Q301.1 (B), R300.1, R309.1
unnamed: Q302.1 (B), R902.1
unnamed: Q302.3 (C), R307.2
unnamed: Q9100.1 (B), R9104.1
unnamed: R203A1.2, U207.3
unnamed: R212.2, U303.3
unnamed: R216.2, U303.1
unnamed: R902.2, U303.6
unnamed: RN100.8 (R7), U100.12 (BGACK), U303.11
unnamed: RN102.1 (R1.1), U107.8
unnamed: FB907.2, RN102.2 (R1.2)
unnamed: RN102.3 (R2.1), U107.6
unnamed: RN102.5 (R3.1), RN102.7 (R4.1), U107.4
unnamed: EMI230.1, RN200.2 (R1), U202.2 (I0a)
unnamed: EMI235.1, RN200.3 (R2), U202.14 (I0d)
unnamed: EMI232.1, RN200.4 (R3), U202.3 (I1a)
unnamed: EMI231.1, RN200.5 (R4), U202.5 (I0b)
unnamed: EMI234.1, RN200.6 (R5), U202.11 (I0c)
unnamed: EMI233.1, RN200.7 (R6), U202.6 (I1b)
unnamed: EMI236.1, RN200.8 (R7), U202.10 (I1c)
unnamed: EMI237.1, RN200.9 (R8), U202.13 (I1d)
unnamed: FB303.2, RN300.4 (R3), U300.39 (S)
unnamed: C726.1, RN700.2 (R1)
unnamed: C722.1, RN700.3 (R2)
unnamed: C720.1, RN700.4 (R3)
unnamed: C719.1, RN700.5 (R4)
unnamed: C717.1, RN700.6 (R5)
unnamed: C716.1, RN700.7 (R6)
unnamed: C714.1, RN700.8 (R7)
unnamed: C713.1, RN700.9 (R8)
unnamed: C711.1, RN700.10 (R9)
unnamed: C744.1, RN701.2 (R1)
unnamed: C742.1, RN701.3 (R2)
unnamed: C740.1, RN701.4 (R3)
unnamed: C738.1, RN701.5 (R4)
unnamed: C736.1, RN701.6 (R5)
unnamed: C734.1, RN701.7 (R6)
unnamed: C732.1, RN701.8 (R7)
unnamed: C730.1, RN701.9 (R8)
unnamed: C728.1, RN701.10 (R9)
unnamed: C791.1, RN702.2 (R1)
unnamed: C790.1, RN702.3 (R2)
unnamed: C758.1, RN702.4 (R3)
unnamed: C756.1, RN702.5 (R4)
unnamed: C754.1, RN702.6 (R5)
unnamed: C752.1, RN702.7 (R6)
unnamed: C750.1, RN702.8 (R7)
unnamed: C748.1, RN702.9 (R8)
unnamed: C746.1, RN702.10 (R9)
unnamed: C770.1, RN703.2 (R1)
unnamed: C768.1, RN703.3 (R2)
unnamed: C766.1, RN703.4 (R3)
unnamed: C764.1, RN703.5 (R4)
unnamed: C762.1, RN703.6 (R5)
unnamed: C760.1, RN703.7 (R6)
unnamed: C796.1, RN703.8 (R7)
unnamed: C794.1, RN703.9 (R8)
unnamed: C793.1, RN703.10 (R9)
unnamed: C789.1, RN704.2 (R1)
unnamed: C787.1, RN704.3 (R2)
unnamed: C786.1, RN704.4 (R3)
unnamed: C784.1, RN704.5 (R4)
unnamed: C782.1, RN704.6 (R5)
unnamed: C780.1, RN704.7 (R6)
unnamed: C778.1, RN704.8 (R7)
unnamed: C776.1, RN704.9 (R8)
unnamed: CN700.B11, CN701.B11, CN702.B11, RN705.2 (R1)
unnamed: CN700.B12, CN701.B12, CN702.B12, RN705.3 (R2)
unnamed: CN700.B13, CN701.B13, CN702.B13, RN705.4 (R3)
unnamed: CN700.B14, CN701.B14, CN702.B14, RN705.5 (R4)
unnamed: CN700.D1, CN701.D1, CN702.D1, RN705.6 (R5)
unnamed: CN700.D2, CN701.D2, CN702.D2, RN705.7 (R6)
unnamed: CN700.C9, CN701.C9, CN702.C9, RN705.8 (R7)
unnamed: CN700.C10, CN701.C10, CN702.C10, RN705.9 (R8)
unnamed: C815.1, RN802.1 (R1.1), RN802.4 (R2.2), RN802.5 (R3.1), U805.5 (+), U805.7 (+), U805.9 (+)
unnamed: RN802.6 (R3.2), RN802.7 (R4.1), U805.11 (+)
unnamed: RN802.8 (R4.2), RN802.10 (R5.2), U805.8 (-), U805.13
unnamed: RN902.3 (R2.1), U107.12
unnamed: RN902.5 (R3.1), U107.10
unnamed: RN902.7 (R4.1), U107.2
unnamed: RN907B1.2, U302.8
unnamed: RN908.2 (R1), U605.2 (A0)
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
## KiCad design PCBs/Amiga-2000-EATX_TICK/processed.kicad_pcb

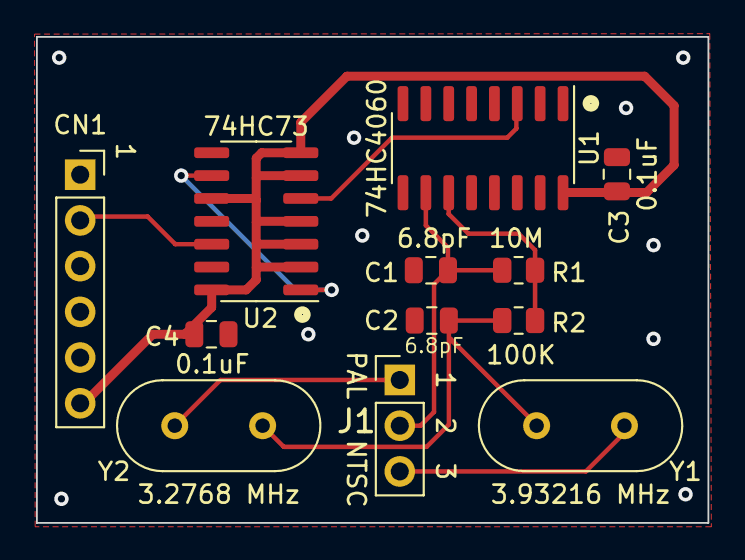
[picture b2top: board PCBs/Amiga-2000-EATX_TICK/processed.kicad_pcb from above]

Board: 2 copper layers, 37.3 x 27.0 mm, 12 parts (0 on the bottom side), 10 nets.

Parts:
C1, C2: 6.8pF; C_0805_2012Metric
C3, C4: 0.1uF; C_0805_2012Metric
CN1: To_Amiga; PinSocket_1x06_P2.54mm_Vertical
J1: Conn_01x03_Male; PinHeader_1x03_P2.54mm_Vertical
R1: 10M; R_0805_2012Metric
R2: 100K; R_0805_2012Metric
U1: 74HC4060; SOIC-16_3.9x9.9mm_P1.27mm
U2: 74HC73; SOIC-14_3.9x8.7mm_P1.27mm
Y1: 3.93216 MHz; Crystal_HC49-U_Vertical
Y2: 3.2768 MHz; Crystal_HC49-U_Vertical

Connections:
+5V: C3.1, C4.2, CN1.6, U1.16 (V+), U2.2 (~R), U2.3 (K), U2.4 (VCC), U2.6 (~R), U2.7 (J), U2.10 (K), U2.14 (J)
/TBASE: CN1.2, U2.12 (Q)
GND: C1.2, C2.2, C3.2, C4.1, CN1.3, U1.8 (GND), U1.12 (MR), U2.11 (GND)
unnamed: C1.1, J1.2, R1.1, U1.10 (RTC)
unnamed: C2.1, R2.2, Y1.2, Y2.1
unnamed: J1.1, Y2.2
unnamed: J1.3, Y1.1
unnamed: R1.2, R2.1, U1.11 (RS)
unnamed: U1.3 (Q13), U2.5 (C)
unnamed: U2.1 (C), U2.9 (Q)

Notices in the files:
PCBs/Awesome-Keebs_torn_left/processed.kicad_pcb:
Torn keyboard licensed under CC BY-NC 4.0
